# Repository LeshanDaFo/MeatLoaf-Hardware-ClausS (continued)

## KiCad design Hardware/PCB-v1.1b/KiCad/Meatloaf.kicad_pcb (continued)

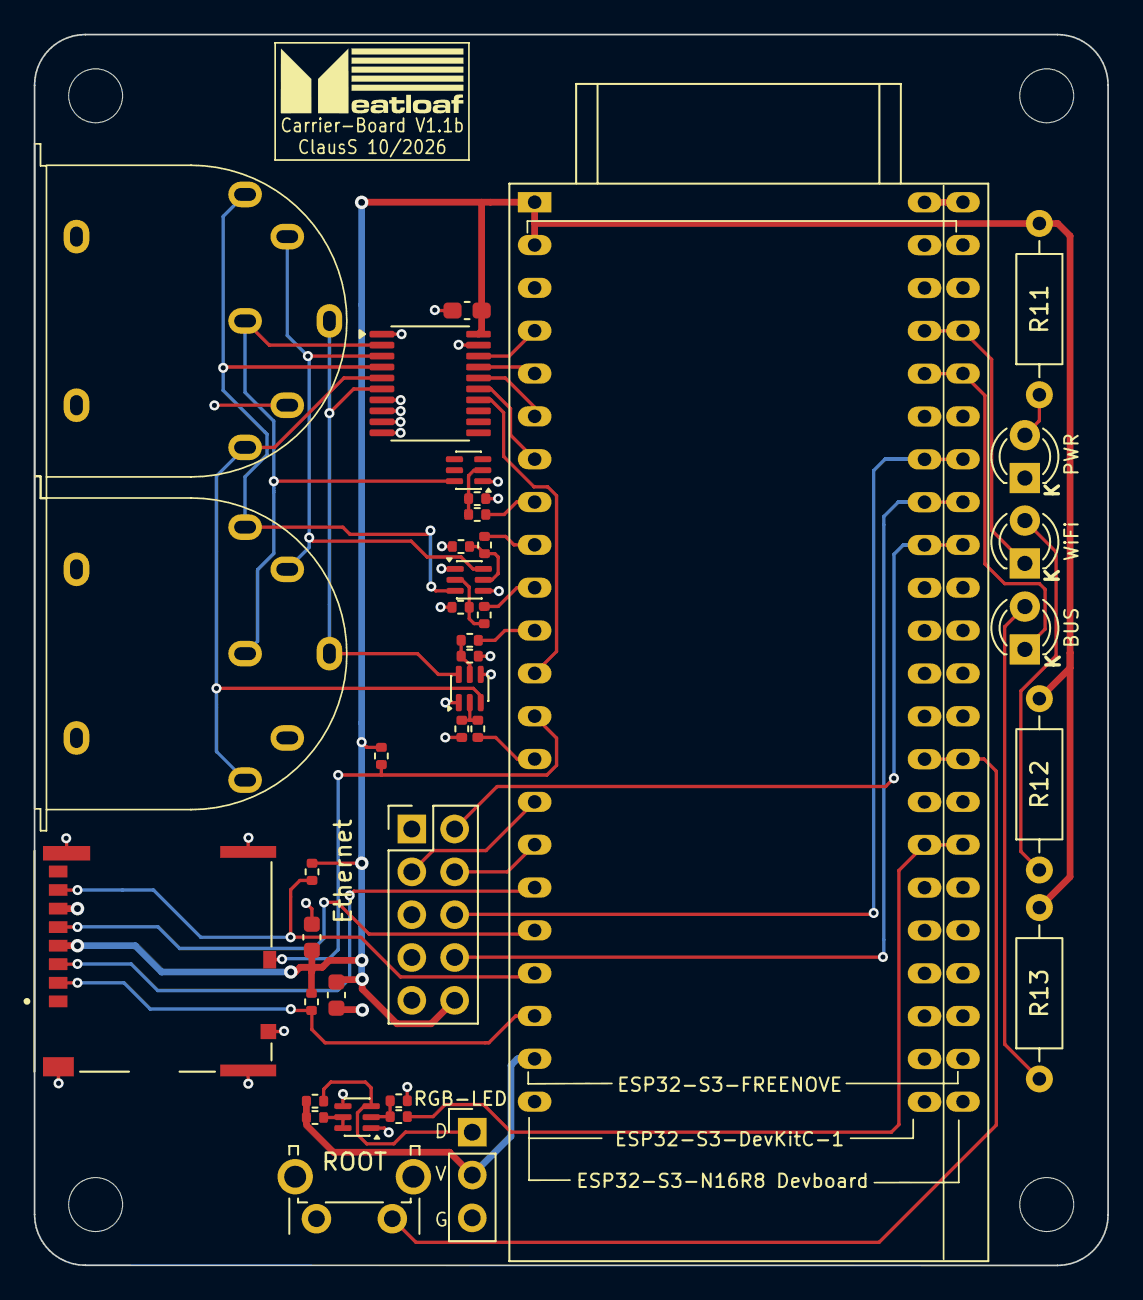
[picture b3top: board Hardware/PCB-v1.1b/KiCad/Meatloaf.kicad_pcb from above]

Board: 2 copper layers, 63.7 x 73.0 mm, 42 parts (0 on the bottom side), 43 nets.

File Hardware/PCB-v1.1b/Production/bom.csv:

Designator,Footprint,Quantity,Value,LCSC Part #
C1,0603,1,10uF,
"C2, C3",0603,2,100nF,
J3,MOLEX_503398-1892,1,503398-1892,C428492
"Q6, Q7, Q8, Q9",SOT-363_SC-70-6,4,BC847BS,
"R20, R31, R32, R35",0402,4,1k5,
"R21, R22, R25, R26, R33, R34, R36, R38, R39, R40",0402,10,10k,
R23,0402,1,1k,
"R24, R37",0402,2,2k2,
U2,TSSOP-20_4.4x6.5mm_P0.65mm,1,74LVC541A,
